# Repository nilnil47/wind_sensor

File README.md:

## useful links

angle 7 click datasheet - https://www.mikroe.com/angle-7-click
angle 7 click schematic - https://download.mikroe.com/documents/add-on-boards/click/angle_7_click/Angle_7_click_v101_Schematic.PDF

AS5600 (the main componnet) datasheet - https://www.snapeda.com/parts/AS5600/Ams%20AG/datasheet/

AS5600 footprint and schematic can be downloaded from ultralibrarian

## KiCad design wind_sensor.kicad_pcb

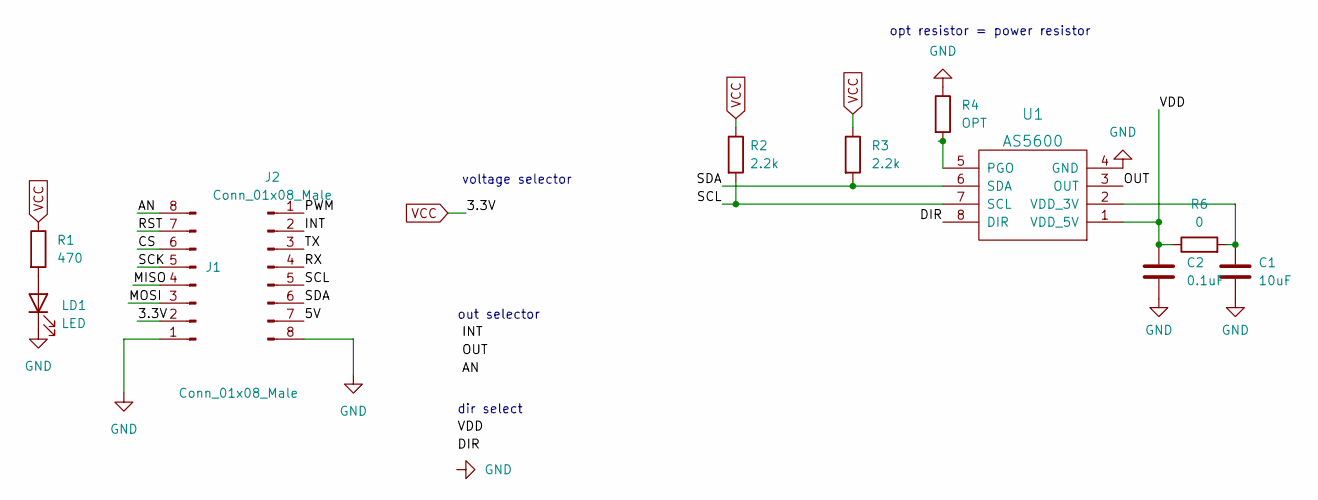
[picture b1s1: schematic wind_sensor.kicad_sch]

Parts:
C1: 10uF; CP_Elec_6.3x3
C2: 0.1uF; CP_Elec_6.3x3
J1, J2: Conn_01x08_Male; PinHeader_1x08_P2.54mm_Vertical
LD1: LED; LED-APA102-2020
R1: 470; R_Axial_DIN0207_L6.3mm_D2.5mm_P2.54mm_Vertical
R2, R3: 2.2k; R_Axial_DIN0204_L3.6mm_D1.6mm_P1.90mm_Vertical
R4: OPT; R_Axial_DIN0207_L6.3mm_D2.5mm_P2.54mm_Vertical
R6: 0; R_Axial_DIN0204_L3.6mm_D1.6mm_P1.90mm_Vertical
U1: AS5600; AS5600L-ASOM_AMS

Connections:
/5V: J2.7
/AN: J1.8
/CS: J1.6
/DIR: U1.8 (DIR)
/INT: J2.2
/MISO: J1.4
/MOSI: J1.3
/OUT: U1.3 (OUT)
/PWM: J2.1
/RST: J1.7
/RX: J2.4
/SCK: J1.5
/SCL: J2.5, R2.2, U1.7 (SCL)
/SDA: J2.6, R3.2, U1.6 (SDA)
/TX: J2.3
/VDD: C2.1, R6.1, U1.1 (VDD_5V)
GND: C1.2, C2.2, J1.1, J2.8, LD1.1 (K), R4.1, U1.4 (GND)
unnamed: C1.1, R6.2, U1.2 (VDD_3V)
unnamed: LD1.2 (A), R1.2
unnamed: R4.2, U1.5 (PGO)

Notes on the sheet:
dir select
voltage selector
out selector
opt resistor = power resistor

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
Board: 2 copper layers, 11 parts (0 on the bottom side), 8 nets, no tracks yet.

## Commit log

2023-08-13 first commit - schematic and pcb with 3.3 and 5
2023-08-13 remove regulator
2023-08-13 add another led in schematic
2023-08-19 replace 0 ohm ressistor with direct connection
